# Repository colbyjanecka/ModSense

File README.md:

# ModSense: Motion-Based CV for Eurorack

**Have you ever wanted to control your Eurorack patch with just your presence, or maybe add an invisible whammy bar to your ModCaster?**  Well, this 6 HP module allows you to use your bodily movement within your patch, enabling quick and effective live-performance control options.

## Schematic

## Features

- 4 x Programmable CV Out (0-12v)
- Generates Trigger Output when object presence is detected/changed
- Ultrasonic ranging transducer provides multi-functional outputs:
  - Detection area: 2cm~500cm;  precision: down to 0.3 cm
  - Example: distance and speed of detected object

## Parts

- Raspberry Pi Pico (RP2040)
- MCP4728 12 Bit I2C DAC
- TL074 Op-Amp
- HC-SR04 Ultrasonic Module
- Infrared Photoelectric Module (3-pin)

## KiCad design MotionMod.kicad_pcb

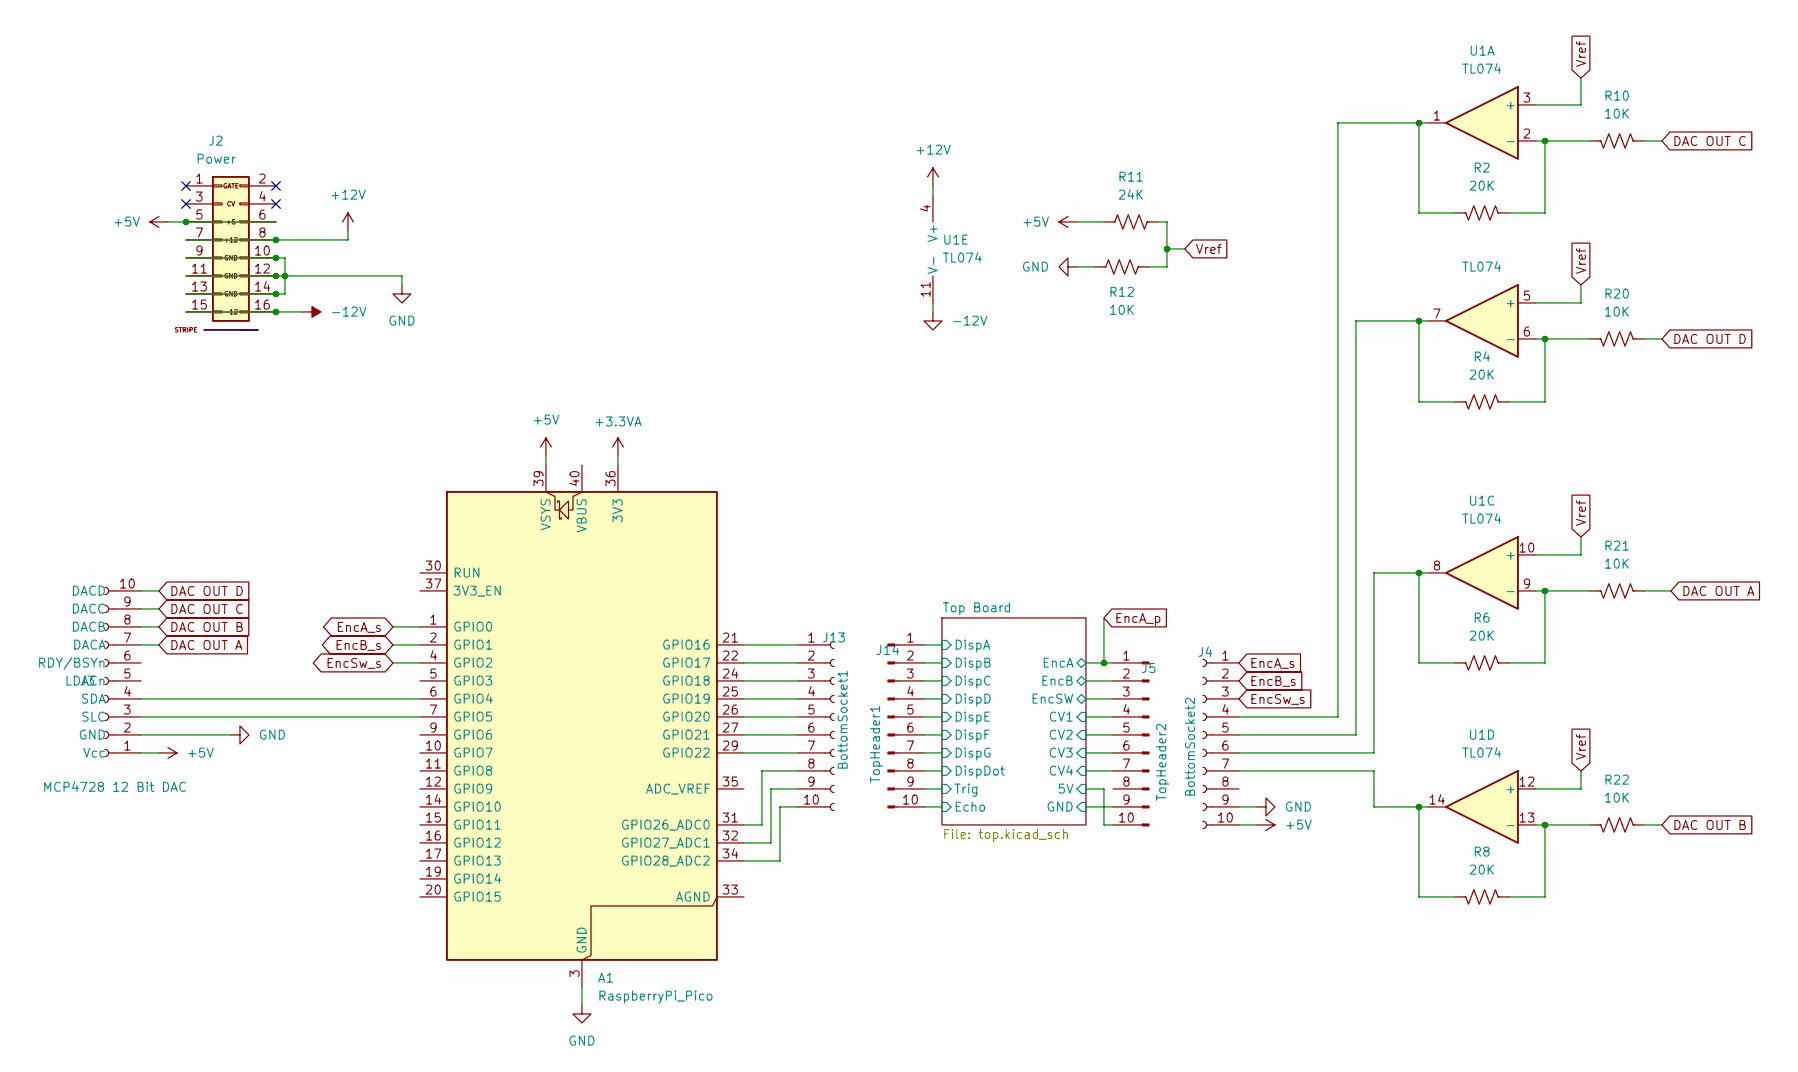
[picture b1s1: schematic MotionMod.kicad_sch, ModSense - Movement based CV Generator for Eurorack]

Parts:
A1: RaspberryPi_Pico; RaspberryPi_Pico_SMD_HandSolder
J2: Power; Pins_2x08_2.54mm_TH_EuroPower; Part Number 1-1602FBV0T
J3: MCP4728 12 Bit DAC; PinHeader_1x10_P2.54mm_Vertical
J4: BottomSocket2; PinSocket_1x10_P2.54mm_Vertical
J5: TopHeader2; PinHeader_1x10_P2.54mm_Vertical
J13: BottomSocket1; PinSocket_1x10_P2.54mm_Vertical
J14: TopHeader1; PinHeader_1x10_P2.54mm_Vertical
R2, R4, R6, R8: 20K; R_Axial_DIN0207_L6.3mm_D2.5mm_P7.62mm_Horizontal
R10, R12, R20, R21, R22: 10K; R_Axial_DIN0207_L6.3mm_D2.5mm_P7.62mm_Horizontal
R11: 24K; R_Axial_DIN0207_L6.3mm_D2.5mm_P7.62mm_Horizontal
U1: TL074; DIP-14_W7.62mm_LongPads

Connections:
+3.3VA: A1.36 (3V3)
+5V: A1.39 (VSYS), J2.5 (+12V), J2.6, J3.1 (Vcc), J4.10, J5.10, R11.1; also elsewhere on the board
+12V: J2.7 (12V), J2.8 (+12V), U1.4 (V+)
-12V: J2.15 (-12V), J2.16, U1.11 (V-)
/Top Board/CV1: J5.4; also elsewhere on the board
/Top Board/CV2: J5.5; also elsewhere on the board
/Top Board/CV3: J5.6; also elsewhere on the board
/Top Board/CV4: J5.7; also elsewhere on the board
/Top Board/DispA: J14.1; also elsewhere on the board
/Top Board/DispB: J14.2; also elsewhere on the board
/Top Board/DispC: J14.3; also elsewhere on the board
/Top Board/DispD: J14.4; also elsewhere on the board
/Top Board/DispDot: J14.8; also elsewhere on the board
/Top Board/DispE: J14.5; also elsewhere on the board
/Top Board/DispF: J14.6; also elsewhere on the board
/Top Board/DispG: J14.7; also elsewhere on the board
/Top Board/Echo: J14.10; also elsewhere on the board
/Top Board/EncB: J5.2; also elsewhere on the board
/Top Board/EncSW: J5.3; also elsewhere on the board
/Top Board/Trig: J14.9; also elsewhere on the board
DAC OUT A: J3.7 (DACA), R21.1
DAC OUT B: J3.8 (DACB), R22.1
DAC OUT C: J3.9 (DACC), R10.1
DAC OUT D: J3.10 (DACD), R20.1
EncA_p: J5.1; also elsewhere on the board
EncA_s: A1.1 (GPIO0), J4.1
EncB_s: A1.2 (GPIO1), J4.2
EncSw_s: A1.4 (GPIO2), J4.3
GND: A1.3 (GND), A1.8 (GND), A1.13 (GND), A1.18 (GND), A1.23 (GND), A1.28 (GND), A1.38 (GND), J2.9 (GND), J2.10 (GND), J2.11 (GND), J2.12 (GND), J2.13 (-12), J2.14 (-12V), J3.2 (GND), J4.9, J5.9, R12.1; also elsewhere on the board
unnamed: A1.6 (GPIO4), J3.4 (SDA)
unnamed: A1.7 (GPIO5), J3.3 (SLC)
unnamed: A1.21 (GPIO16), J13.1
unnamed: A1.22 (GPIO17), J13.2
unnamed: A1.24 (GPIO18), J13.3
unnamed: A1.25 (GPIO19), J13.4
unnamed: A1.26 (GPIO20), J13.5
unnamed: A1.27 (GPIO21), J13.6
unnamed: A1.29 (GPIO22), J13.7
unnamed: A1.31 (GPIO26_ADC0), J13.8
unnamed: A1.32 (GPIO27_ADC1), J13.9
unnamed: A1.34 (GPIO28_ADC2), J13.10
unnamed: J4.4, R2.2, U1.1
unnamed: J4.5, R4.2, U1.7
unnamed: J4.6, R6.2, U1.8
unnamed: J4.7, R8.2, U1.14
unnamed: R2.1, R10.2, U1.2 (-)
unnamed: R4.1, R20.2, U1.6 (-)
unnamed: R6.1, R21.2, U1.9 (-)
unnamed: R8.1, R22.2, U1.13 (-)
Vref: R11.2, R12.2, U1.3 (+), U1.5 (+), U1.10 (+), U1.12 (+)

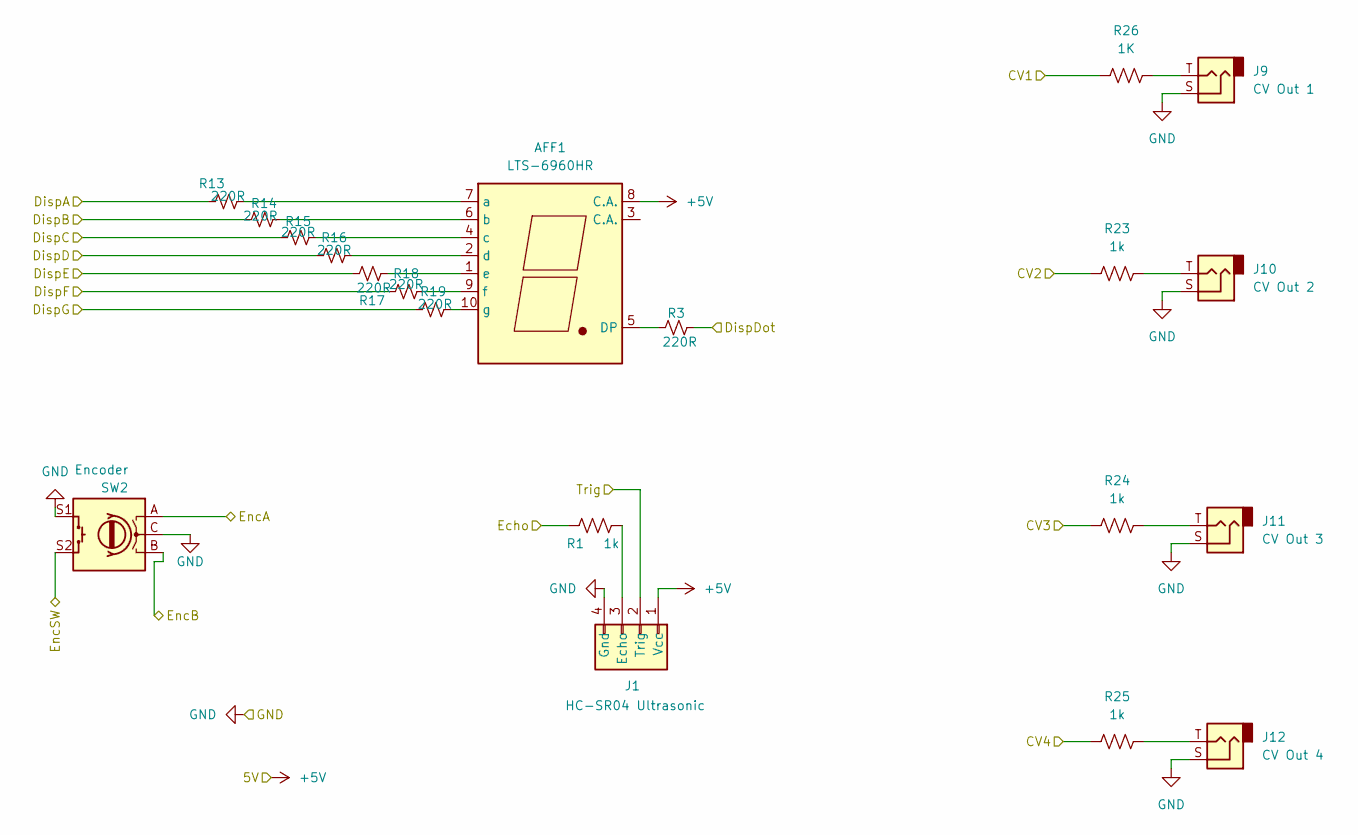
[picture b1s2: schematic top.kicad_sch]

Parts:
AFF1: LTS-6960HR; 7SegmentLED_LTS6760_LTS6780
J1: HC-SR04 Ultrasonic; Ultrasonic_Module_HC-SR04
J9: CV Out 1; Jack_3.5mm_QingPu_WQP-PJ398SM_Vertical_CircularHoles
J10: CV Out 2; Jack_3.5mm_QingPu_WQP-PJ398SM_Vertical_CircularHoles
J11: CV Out 3; Jack_3.5mm_QingPu_WQP-PJ398SM_Vertical_CircularHoles
J12: CV Out 4; Jack_3.5mm_QingPu_WQP-PJ398SM_Vertical_CircularHoles
R1, R23, R24, R25: 1k; R_Axial_DIN0207_L6.3mm_D2.5mm_P7.62mm_Horizontal
R3, R13, R14, R15, R16, R17, R18, R19: 220R; R_Axial_DIN0207_L6.3mm_D2.5mm_P7.62mm_Horizontal
R26: 1K; R_Axial_DIN0207_L6.3mm_D2.5mm_P7.62mm_Horizontal
SW2: Encoder; ENC_SPST_12mm

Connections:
+5V: AFF1.8 (C.A.), J1.1 (Vcc); also elsewhere on the board
/Top Board/CV1: R26.1; also elsewhere on the board
/Top Board/CV2: R23.1; also elsewhere on the board
/Top Board/CV3: R24.1; also elsewhere on the board
/Top Board/CV4: R25.1; also elsewhere on the board
/Top Board/DispA: R13.1; also elsewhere on the board
/Top Board/DispB: R14.1; also elsewhere on the board
/Top Board/DispC: R15.1; also elsewhere on the board
/Top Board/DispD: R16.1; also elsewhere on the board
/Top Board/DispDot: R3.2; also elsewhere on the board
/Top Board/DispE: R17.1; also elsewhere on the board
/Top Board/DispF: R18.1; also elsewhere on the board
/Top Board/DispG: R19.1; also elsewhere on the board
/Top Board/Echo: R1.1; also elsewhere on the board
/Top Board/EncB: SW2.B; also elsewhere on the board
/Top Board/EncSW: SW2.S2; also elsewhere on the board
/Top Board/Trig: J1.2 (Trig); also elsewhere on the board
EncA_p: SW2.A; also elsewhere on the board
GND: J1.4 (Gnd), J9.S, J10.S, J11.S, J12.S, SW2.C, SW2.S1; also elsewhere on the board
unnamed: AFF1.5 (DP), R3.1
unnamed: AFF1.7 (a), R13.2
unnamed: AFF1.6 (b), R14.2
unnamed: AFF1.4 (c), R15.2
unnamed: AFF1.2 (d), R16.2
unnamed: AFF1.1 (e), R17.2
unnamed: AFF1.9 (f), R18.2
unnamed: AFF1.10 (g), R19.2
unnamed: J1.3 (Echo), R1.2
unnamed: J9.T, R26.2
unnamed: J10.T, R23.2
unnamed: J11.T, R24.2
unnamed: J12.T, R25.2

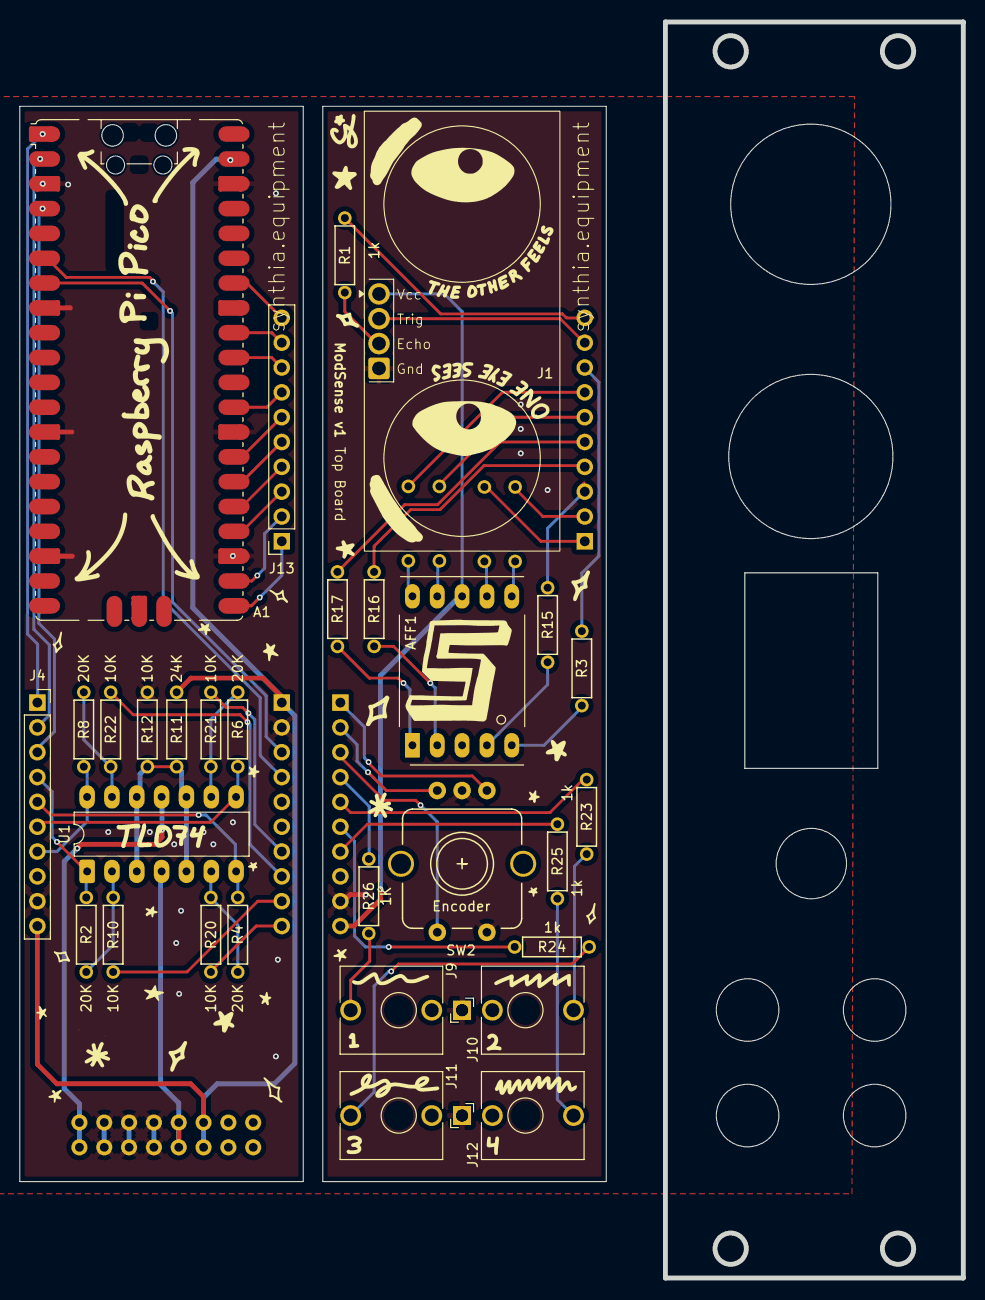
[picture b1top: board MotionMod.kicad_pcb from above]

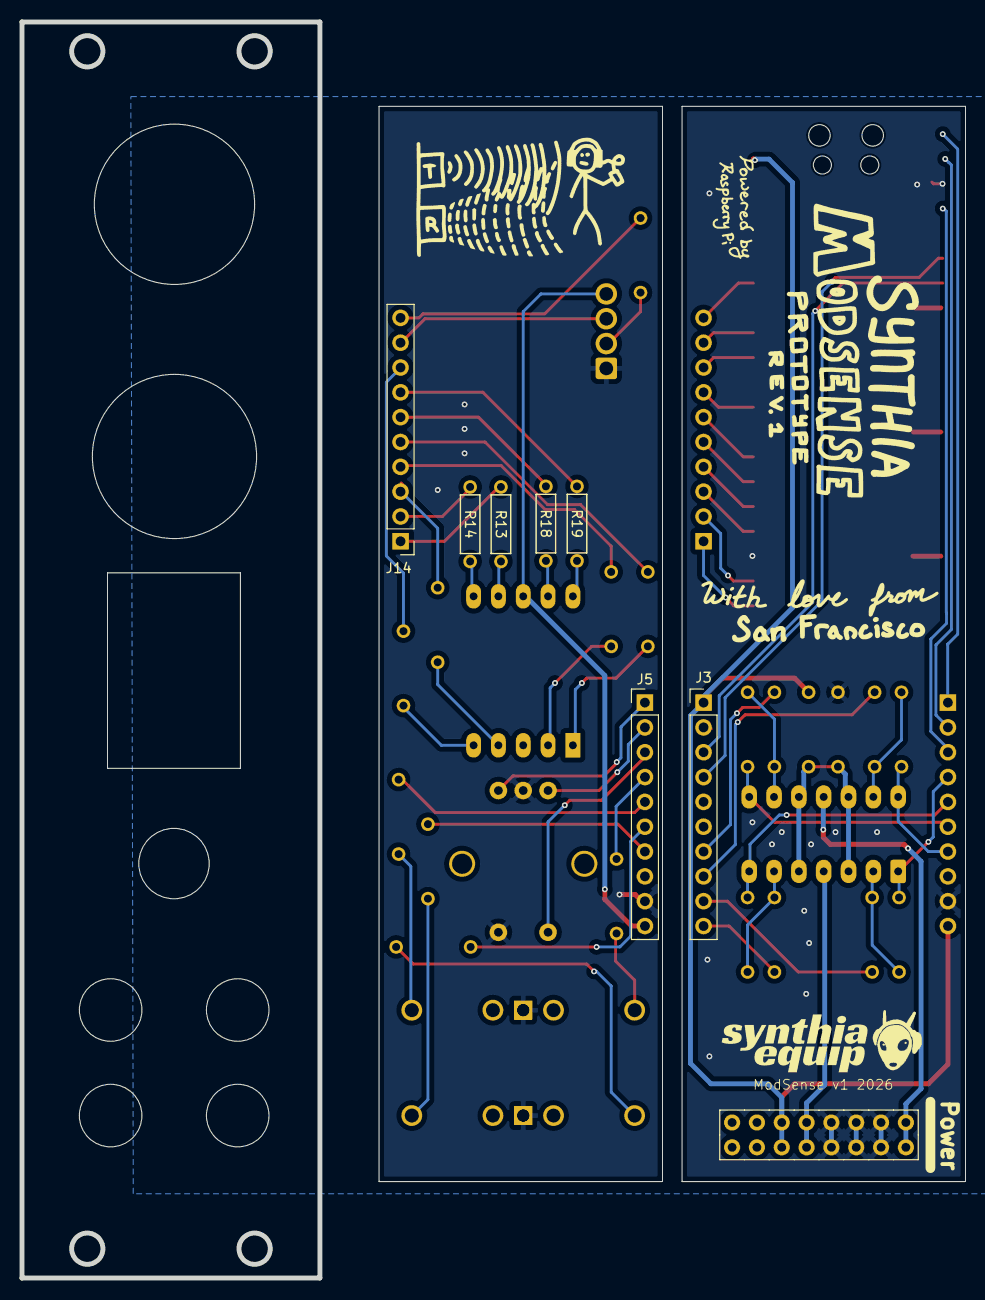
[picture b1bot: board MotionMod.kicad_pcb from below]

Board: 2 copper layers, 96.5 x 128.5 mm, 38 parts (8 on the bottom side), 62 nets.

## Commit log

2026-03-31 rev 1
2026-03-31 added sch image and pdf
2026-03-31 embed sch image in disc
2026-03-31 updated gitignore
2026-03-31 removed auto_saved_files from being tracked
2026-03-31 Enhance README with detailed module information
    Expanded README with module description, features, and parts list.
2026-03-31 implemented initial test code
2026-04-17 final gerbers for v1
